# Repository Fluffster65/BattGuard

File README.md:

# BattGuard

BattGuard is a KiCad hardware design for a solar-assisted battery charger and power-management board. The project combines a 12 V charging path, protected power inputs, regulated system rails, battery monitoring, and an ESP32-S3 control interface on one board.

The design has progressed from an initial schematic into a nearly complete, routed PCB project. The current revision includes cleaned-up routing, test points, connector and switch footprints, populated protection and filtering components, and a shared component library with symbols, footprints, and 3D models.

## What the board includes

- **Battery charging:** BQ25756-based charger and power-path circuitry, with solar/charge input support and thermistor monitoring.
- **Power conversion:** 5 V buck regulation, 3.3 V regulation, and a boost circuit for the higher-voltage charging rail.
- **Protection:** reverse-polarity and reverse-current protection, transient suppression, input fusing, and protected power switching.
- **Measurement:** INA226 current/voltage monitoring with a dedicated shunt and I²C connectivity.
- **Control and telemetry:** ESP32-S3 header, GPIO breakouts, charge-enable control, status indicators, pushbuttons, and external connectors.
- **Serviceability:** labeled test points, modular connectors, and a board layout prepared for review and fabrication.

## Project status

The schematic and PCB are actively maintained and are at the late-stage design-review/fabrication-preparation phase. Recent work has focused on final trace routing, power-trace sizing, test-point and control-interface placement, silkscreen cleanup, and KiCad DRC cleanup. Fabrication, assembly, bring-up, and electrical validation are still separate steps and should not be inferred from the design files alone.

## Repository layout

```text
board/
├── BattGuard/       # Main schematic, PCB, rules, and project files
├── Datasheets/      # Component datasheets used during design
├── libs/
│   ├── 3dmodels/    # Local STEP models
│   ├── footprints/  # Shared TeamLib footprints
│   └── symbols/     # Shared KiCad symbols
├── fp-lib-table      # Project footprint-library configuration
└── sym-lib-table     # Project symbol-library configuration
```

The main KiCad project is `board/BattGuard/BattGuard.kicad_pro`. Library paths are project-relative, so the shared symbols, footprints, and models travel with the repository and do not require machine-specific absolute paths.

## Opening the project

1. Clone the repository.
2. Open `board/BattGuard/BattGuard.kicad_pro` in KiCad.
3. Confirm that the project loads the committed `TeamLib` symbol and footprint libraries.
4. Review the schematic, PCB, and design rules together before making layout changes.

## Contributing

When adding or changing a component, keep its symbol, footprint, and 3D model in the shared library structure under `board/libs/`. Verify that the part loads correctly in KiCad and that the schematic and PCB remain consistent. Avoid simultaneous edits to the same schematic sheet or PCB layout region, and tag known fabrication snapshots so board revisions remain traceable.

See [CONTRIBUTING.md](CONTRIBUTING.md) for the component-library workflow.

## Team

BattGuard is a Team 23 senior-design project by Brendan Duffy, Jon Mensah, Zachary Sydenstricker, and Tyler Wuthrich.

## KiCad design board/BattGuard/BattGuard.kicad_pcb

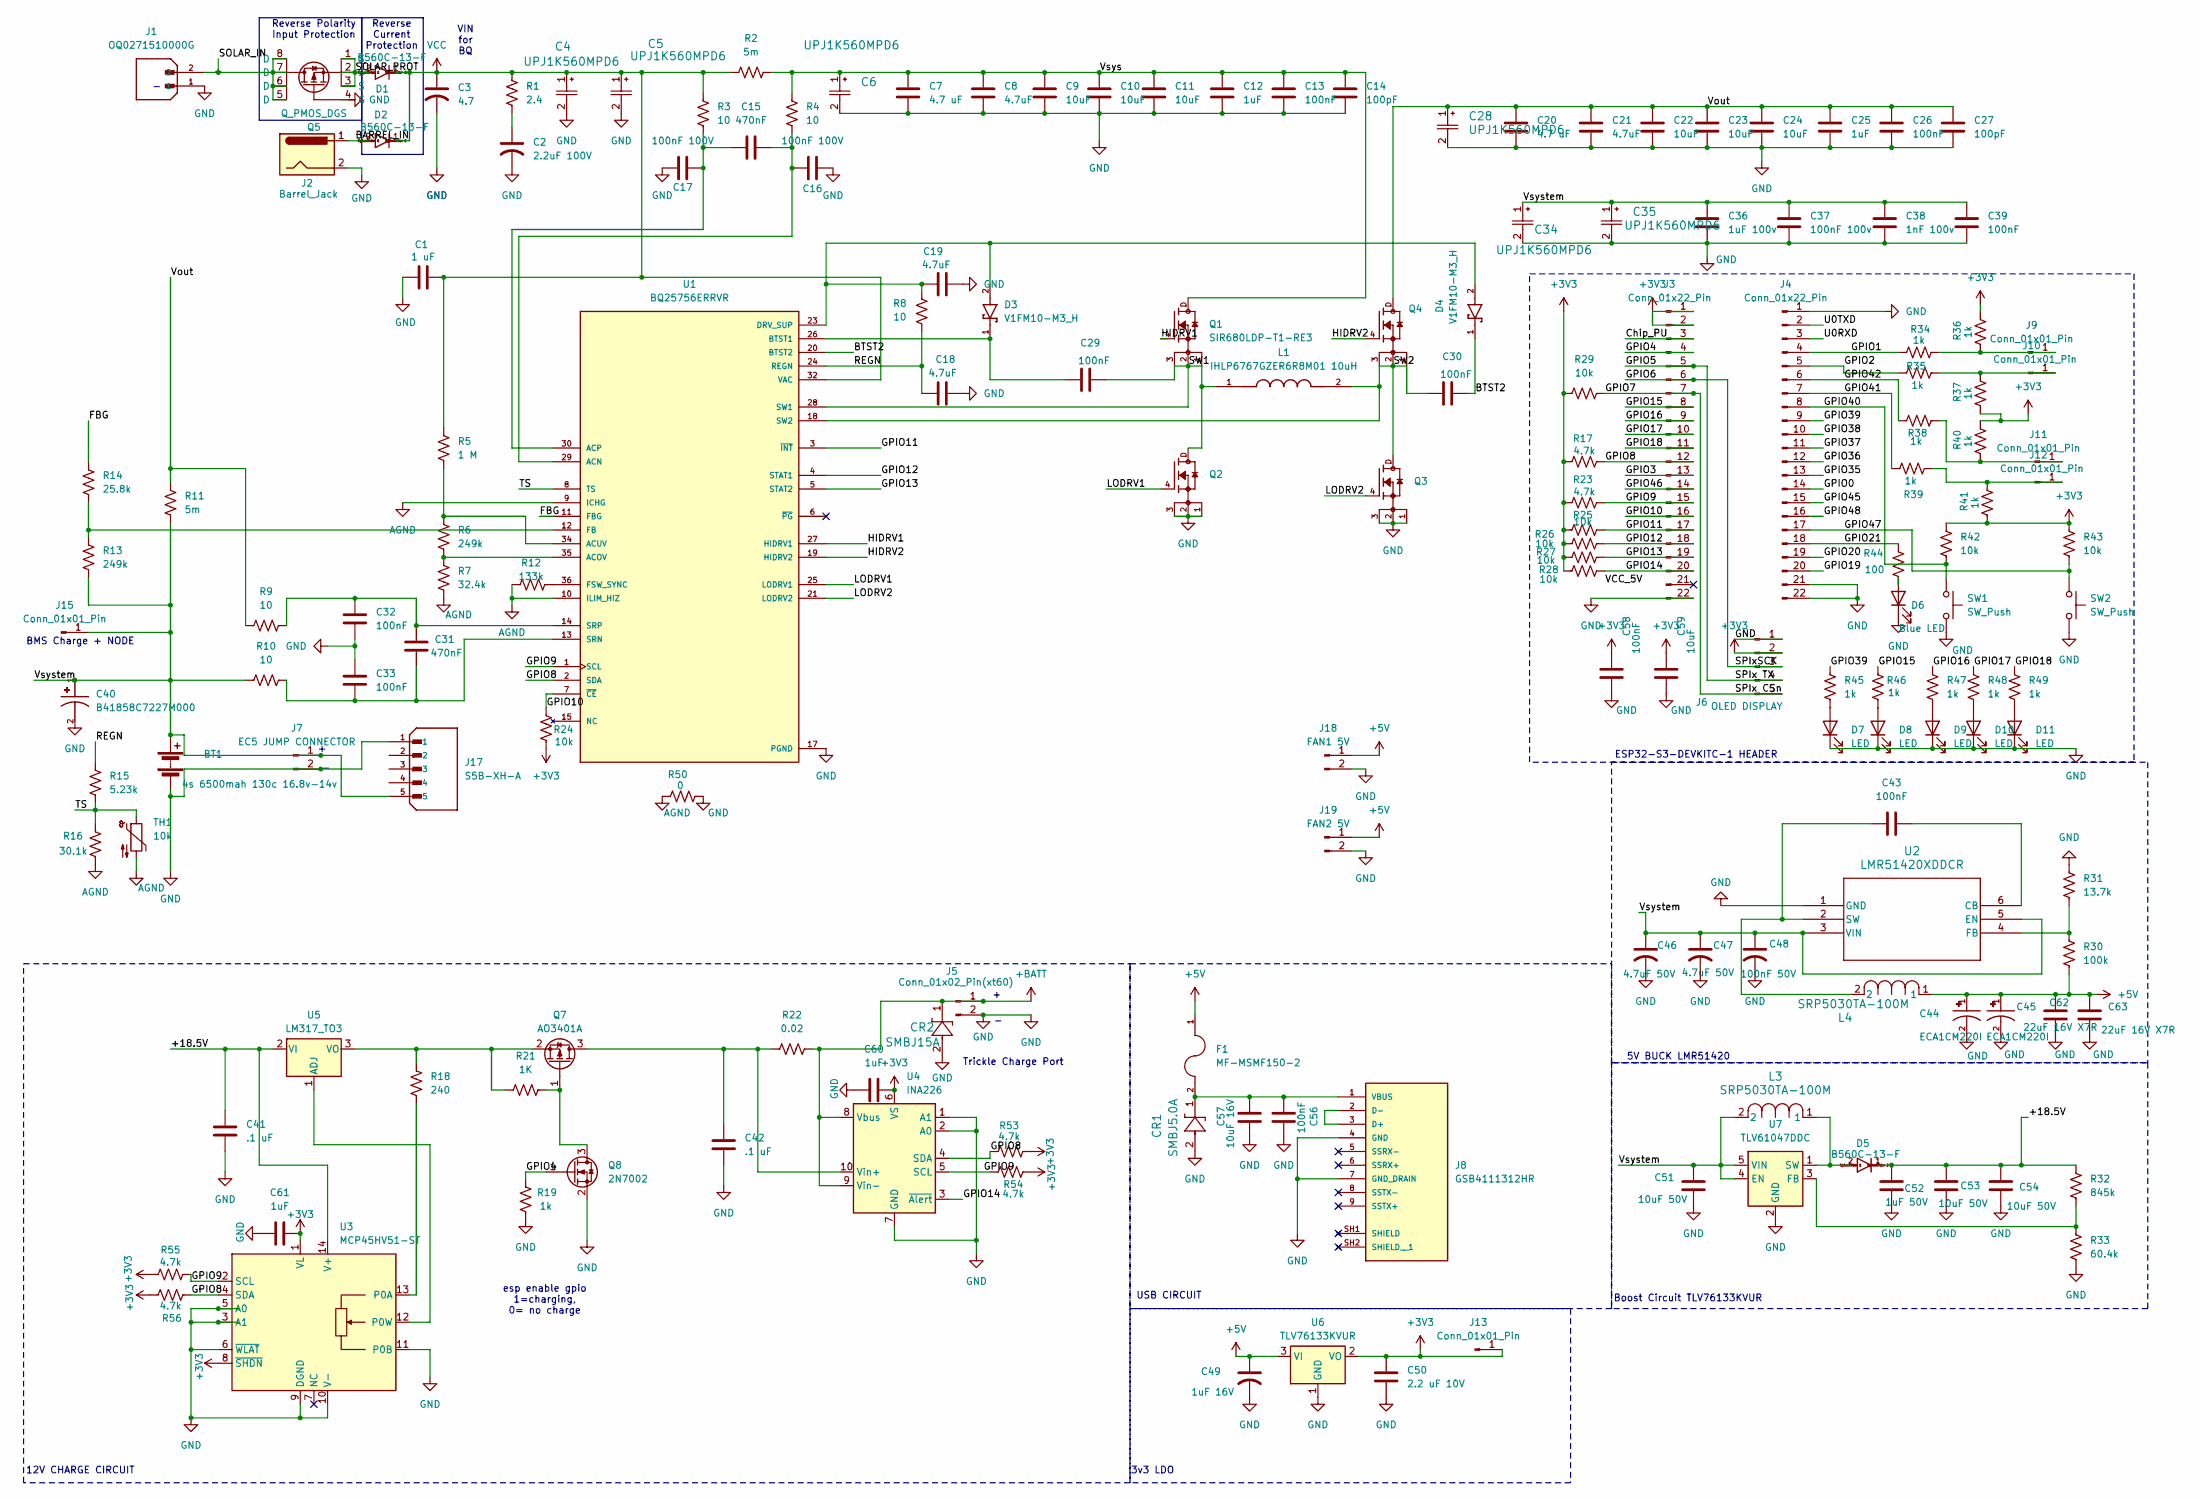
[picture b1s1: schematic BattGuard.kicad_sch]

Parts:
BT1: 4s 6500mah 130c 16.8v-14v
C1: 1 uF; C_0805_2012Metric
C2: 2.2uF 100V; C_1206_3216Metric
C3: 4.7; C_1210_3225Metric_Pad1.33x2.70mm_HandSolder
C4, C5, C6, C28, C34, C35: UPJ1K560MPD6; CAP_UPJ_10X15_NCH
C7, C20: 4.7 uF; C_0805_2012Metric
C8, C18, C19, C21: 4.7uF; C_0805_2012Metric
C9, C10, C11: 10uF; C_1210_3225Metric_Pad1.33x2.70mm_HandSolder
C12, C25, C60, C61: 1uF; C_0805_2012Metric
C13, C26, C29, C30, C32, C33, C39, C43, C56, C58: 100nF; C_0805_2012Metric
C14, C27: 100pF; C_0805_2012Metric
C15, C31: 470nF; C_0805_2012Metric
C16, C17: 100nF 100V; C_0805_2012Metric
C22, C23, C24, C59: 10uF; C_0805_2012Metric
C36: 1uF 100v; C_0805_2012Metric
C37: 100nF 100v; C_0805_2012Metric
C38: 1nF 100v; C_0805_2012Metric
C40: B41858C7227M000; CP_Radial_D10.0mm_P2.50mm; PARTREV 2018-10
C41, C42: .1 uF; C_0805_2012Metric
C44, C45: ECA1CM220I; CP_Radial_D10.0mm_P2.50mm; PARTREV 20-DEC-19
C46, C47: 4.7uF 50V; C_0805_2012Metric
C48: 100nF 50V; C_0805_2012Metric
C49: 1uF 16V; C_0805_2012Metric
C50: 2.2 uF 10V; C_0805_2012Metric
C51, C53, C54: 10uF 50V; C_1206_3216Metric_Pad1.33x1.80mm_HandSolder
C52: 1uF 50V; C_0805_2012Metric
C57: 10uF 16V; C_0805_2012Metric
C62, C63: 22uF 16V X7R; C_1206_3216Metric_Pad1.33x1.80mm_HandSolder
CR1: SMBJ5.0A; DO-214AASMB_J-BEND_LTF
CR2: SMBJ15A; DO-214AASMB_J-BEND_LTF
D1, D2, D5: B560C-13-F; D_SMC
D3, D4: V1FM10-M3_H; DIO_V1FM10-M3_H; PARTREV 13-May-2020; DigiKey_Part_Number 112-V1FM10-M3/HCT-ND
D6: Blue LED; LED_D1.8mm_W3.3mm_H2.4mm
D7, D8, D9, D10, D11: LED; LED_D1.8mm_W3.3mm_H2.4mm
F1: MF-MSMF150-2; FUSER_MF-MSMF150-2
J1: OQ0271510000G; PhoenixContact_GMSTBA_2,5_2-G_1x02_P7.50mm_Horizontal; PARTREV J
J2: Barrel_Jack; BarrelJack_CUI_PJ-063AH_Horizontal_CircularHoles
J3, J4: Conn_01x22_Pin; PinSocket_1x22_P2.54mm_Vertical
J5: Conn_01x02_Pin(xt60); AMASS_XT60PW-M_1x02_P7.20mm_Horizontal
J6: OLED DISPLAY; PinHeader_1x05_P2.54mm_Vertical
J7: EC5 JUMP CONNECTOR; AMASS_XT60PW-M_1x02_P7.20mm_Horizontal
J8: GSB4111312HR; USBA_receptacle; PARTREV B
J9, J10, J11, J12, J13: Conn_01x01_Pin; TestPoint_Pad_1.0x1.0mm
J15: Conn_01x01_Pin; MountingHole_2.2mm_M2_DIN965_Pad
J17: S5B-XH-A; JST_S5B-XH-A; PARTREV 27-1-20
J18: FAN1 5V; Wire_Pads_1x02_SMD_2.54
J19: FAN2 5V; Wire_Pads_1x02_SMD_2.54
L1: IHLP6767GZER6R8M01 10uH; L_Vishay_IHLP-6767; PARTREV 24-Nov-2023; DigiKey_Part_Number 541-1257-1-ND
L3, L4: SRP5030TA-100M; L_Bourns_SRP5030T
Q1, Q2, Q3, Q4: SIR680LDP-T1-RE3; TRANS_SIR680LDP-T1-RE3; PARTREV C
Q5: Q_PMOS_DGS; SOIC127P600X175-8N
Q7: AO3401A; SOT-23
Q8: 2N7002; SOT-23
R1: 2.4; R_0805_2012Metric
R2, R11: 5m; R_0805_2012Metric
R3, R4, R8, R9, R10: 10; R_0805_2012Metric
R5: 1 M; R_0805_2012Metric
R6, R13: 249k; R_0805_2012Metric
R7: 32.4k; R_0805_2012Metric
R12: 133k; R_0805_2012Metric
R14: 25.8k; R_0805_2012Metric
R15: 5.23k; R_0805_2012Metric
R16: 30.1k; R_0805_2012Metric
R17, R23, R53, R54, R55, R56: 4.7k; R_0805_2012Metric
R18: 240; R_0805_2012Metric
R19, R34, R35, R36, R37, R38, R39, R40, R41, R45, R46, R47, R48, R49: 1k; R_0805_2012Metric
R21: 1K; R_0805_2012Metric
R22: 0.02; R_0805_2012Metric
R24, R25, R26, R27, R28, R29, R42, R43: 10k; R_0805_2012Metric
R30: 100k; R_0805_2012Metric
R31: 13.7k; R_0805_2012Metric
R32: 845k; R_0805_2012Metric
R33: 60.4k; R_0805_2012Metric
R44: 100; R_0805_2012Metric
R50: 0; R_0805_2012Metric
SW1, SW2: SW_Push; Wire_Pads_1x02_SMD_2.54
TH1: 10k; R_0805_2012Metric
U1: BQ25756ERRVR; IC_BQ25756ERRVR; PARTREV November 2023; DigiKey_Part_Number 296-BQ25756ERRVRCT-ND
U2: LMR51420XDDCR; SOT23_DDC_TEX
U3: MCP45HV51-ST; TSSOP-14_4.4x5mm_P0.65mm
U4: INA226; TSSOP-10_3x3mm_P0.5mm
U5: LM317_TO3; TO-3
U6: TLV76133KVUR; SOT-223-3_TabPin2
U7: TLV61047DDC; SOT-23-5

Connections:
+5V: C44.1, C45.1, C49.1, C62.1, C63.1, F1.1, J18.1, J19.1, L4.1, R30.2, U6.3 (VI); also elsewhere on the board
+BATT: CR2.1, J5.1, R22.2, U4.8 (Vbus), U4.9 (Vin-)
/+18.5V: C41.1, C52.1, C53.1, C54.1, D5.1, R32.1, U3.14 (V+), U5.2 (VI); also elsewhere on the board
/BARREL_IN: D2.2, J2.1
/BTST2: C30.2, D4.1, U1.20 (BTST2)
/Chip_PU: J3.3
/FBG: R14.1, U1.11 (FBG)
/GPIO0: J4.14
/GPIO1: J4.4, R34.1
/GPIO2: J4.5, R35.1
/GPIO3: J3.13
/GPIO4: J3.4, Q8.1 (G), R19.2
/GPIO5: J3.5, J6.4
/GPIO6: J3.6, J6.3
/GPIO7: J3.7, J6.5, R29.2
/GPIO8: J3.12, R17.2, R53.2, R56.1, U1.2 (SDA), U3.4 (SDA), U4.4 (SDA)
/GPIO9: J3.15, R23.2, R54.2, R55.1, U1.1 (SCL), U3.2 (SCL), U4.5 (SCL)
/GPIO10: J3.16, R24.2, U1.7 (~CE)
/GPIO11: J3.17, R25.2, U1.3 (~INT)
/GPIO12: J3.18, R26.2, U1.4 (STAT1)
/GPIO13: J3.19, R27.2, U1.5 (STAT2)
/GPIO14: J3.20, R28.2, U4.3 (~Alert)
/GPIO15: J3.8, R46.1
/GPIO16: J3.9, R47.1
/GPIO17: J3.10, R48.1
/GPIO18: J3.11, R49.1
/GPIO19: J4.20
/GPIO20: J4.19
/GPIO21: J4.18, R44.1
/GPIO35: J4.13
/GPIO36: J4.12
/GPIO37: J4.11
/GPIO38: J4.10
/GPIO39: J4.9, R45.1
/GPIO40: J4.8, R42.2, SW1.1
/GPIO41: J4.7, R39.1
/GPIO42: J4.6, R38.1
/GPIO45: J4.15
/GPIO46: J3.14
/GPIO47: J4.17, R43.2, SW2.1
/GPIO48: J4.16
/HIDRV1: Q1.4, U1.27 (HIDRV1)
/HIDRV2: Q4.4, U1.19 (HIDRV2)
/LODRV1: Q2.4, U1.25 (LODRV1)
/LODRV2: Q3.4, U1.21 (LODRV2)
/REGN: C18.1, R8.1, R15.1, U1.24 (REGN)
/SOLAR_IN: J1.2, Q5.5 (D), Q5.6 (D), Q5.7 (D), Q5.8 (D)
/SOLAR_PROT: D1.2, Q5.1 (S), Q5.2 (S), Q5.3 (S)
/SW1: C29.2, L1.1, Q1.1, Q1.2, Q1.3, Q2.D, U1.28 (SW1)
/SW2: C30.1, L1.2, Q3.D, Q4.1, Q4.2, Q4.3, U1.18 (SW2)
/TS: R15.2, R16.1, TH1.1, U1.8 (TS); also elsewhere on the board
/U0RXD: J4.3
/U0TXD: J4.2
/Vout: C20.1, C21.1, C22.1, C23.1, C24.1, C25.1, C26.1, C27.1, C28.1, Q4.D, R9.1, R11.1
/Vsys: C6.1, C7.1, C8.1, C9.1, C10.1, C11.1, C12.1, C13.1, C14.1, Q1.D, R2.2, R4.1
/Vsystem: BT1.1 (+), C34.1, C35.1, C36.1, C37.1, C38.1, C39.1, C40.1, C46.1, C47.1, C48.1, C51.1, J7.1, J15.1 (Pin_1_1), J17.5, L3.2, R10.1, R11.2, R13.2, U2.3 (VIN), U2.5 (EN), U7.4 (EN), U7.5 (VIN)
AGND: R7.2, R12.1, R16.2, R50.1, TH1.2, U1.9 (ICHG), U1.10 (ILIM_HIZ); also elsewhere on the board
GND: BT1.2 (-), C1.1, C2.2, C3.2, C4.2, C5.2, C6.2, C7.2, C8.2, C9.2, C10.2, C11.2, C12.2, C13.2, C14.2, C16.2, C17.1, C18.2, C19.2, C20.2, C21.2, C22.2, C23.2, C24.2, C25.2, C26.2, C27.2, C28.2, C32.1, C33.2, C34.2, C35.2, C36.2, C37.2, C38.2, C39.2, C40.2, C41.2, C42.2, C44.2, C45.2, C46.2, C47.2, C48.2, C49.2, C50.2, C51.2, C52.2, C53.2, C54.2, C56.2, C57.2, C58.2, C59.2, C60.1, C61.1, C62.2, C63.2, CR1.2, CR2.2, D6.1 (K), D7.1 (K), D8.1 (K), D9.1 (K), D10.1 (K), D11.1 (K), J1.1, J2.2, J3.22, J4.1, J4.21, J4.22, J5.2, J6.1, J7.2, J8.4 (GND), J8.7 (GND_DRAIN), J17.1, J18.2, J19.2, Q2.1, Q2.2, Q2.3, Q3.1, Q3.2, Q3.3, Q5.4 (G), Q8.2 (S), R19.1, R31.1, R33.2, R50.2, SW1.2, SW2.2, U1.17 (PGND), U1.22 (PGND), U1.37 (PGND), U2.1 (GND), U3.3 (A1), U3.5 (A0), U3.6 (~WLAT), U3.9 (DGND), U3.10 (V-), U3.11 (P0B), U4.1 (A1), U4.2 (A0), U4.7 (GND), U6.1 (GND), U7.2 (GND); also elsewhere on the board
unnamed: C2.1, R1.2
unnamed: D6.2 (A), R44.2
unnamed: D7.2 (A), R45.2
unnamed: D8.2 (A), R46.2
unnamed: D9.2 (A), R47.2
unnamed: D10.2 (A), R48.2
unnamed: D11.2 (A), R49.2
unnamed: J8.2 (D-), J8.3 (D+)
unnamed: C56.1, C57.1, CR1.1, F1.2, J8.1 (VBUS)
unnamed: J10.1 (Pin_1_1), R35.2, R37.2
unnamed: J11.1 (Pin_1_1), R38.2, R40.1
unnamed: J12.1 (Pin_1_1), R39.2, R41.2
unnamed: C42.1, Q7.3 (D), R22.1, U4.10 (Vin+)
unnamed: Q7.1 (G), Q8.3 (D), R21.2
unnamed: Q7.2 (S), R18.1, R21.1, U5.3 (VO)
unnamed: C15.2, C16.1, R4.2, U1.29 (ACN)
unnamed: R6.2, R7.1, U1.35 (ACOV)
unnamed: C15.1, C17.2, R3.2, U1.30 (ACP)
unnamed: R5.2, R6.1, U1.34 (ACUV)
unnamed: C29.1, D3.1, U1.26 (BTST1)
unnamed: C19.1, D3.2, D4.2, R8.2, U1.23 (DRV_SUP)
unnamed: R13.1, R14.2, U1.12 (FB)
unnamed: R12.2, U1.36 (FSW_SYNC)
unnamed: C31.1, C33.1, R10.2, U1.13 (SRN)
unnamed: C31.2, C32.2, R9.2, U1.14 (SRP)
unnamed: C43.2, U2.6 (CB)
unnamed: R30.1, R31.2, U2.4 (FB)
unnamed: C43.1, L4.2, U2.2 (SW)
unnamed: R18.2, U3.13 (P0A)
unnamed: U3.12 (P0W), U5.1 (ADJ)
unnamed: R32.2, R33.1, U7.3 (FB)
unnamed: D5.2, L3.1, U7.1 (SW)
VCC: C1.2, C3.1, C4.1, C5.1, D1.1, D2.1, R1.1, R2.1, R3.1, R5.1, U1.32 (VAC), U1.33 (VAC)

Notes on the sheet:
Reverse Current Protection
Boost Circuit TLV76133KVUR
Trickle Charge Port
3v3 LDO
GND
12V CHARGE CIRCUIT
BMS Charge + NODE
ESP32-S3-DEVKITC-1 HEADER
5V BUCK LMR51420
USB CIRCUIT
VIN for BQ
esp enable gpio 1=charging, 0= no charge
Reverse Polarity Input Protection

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
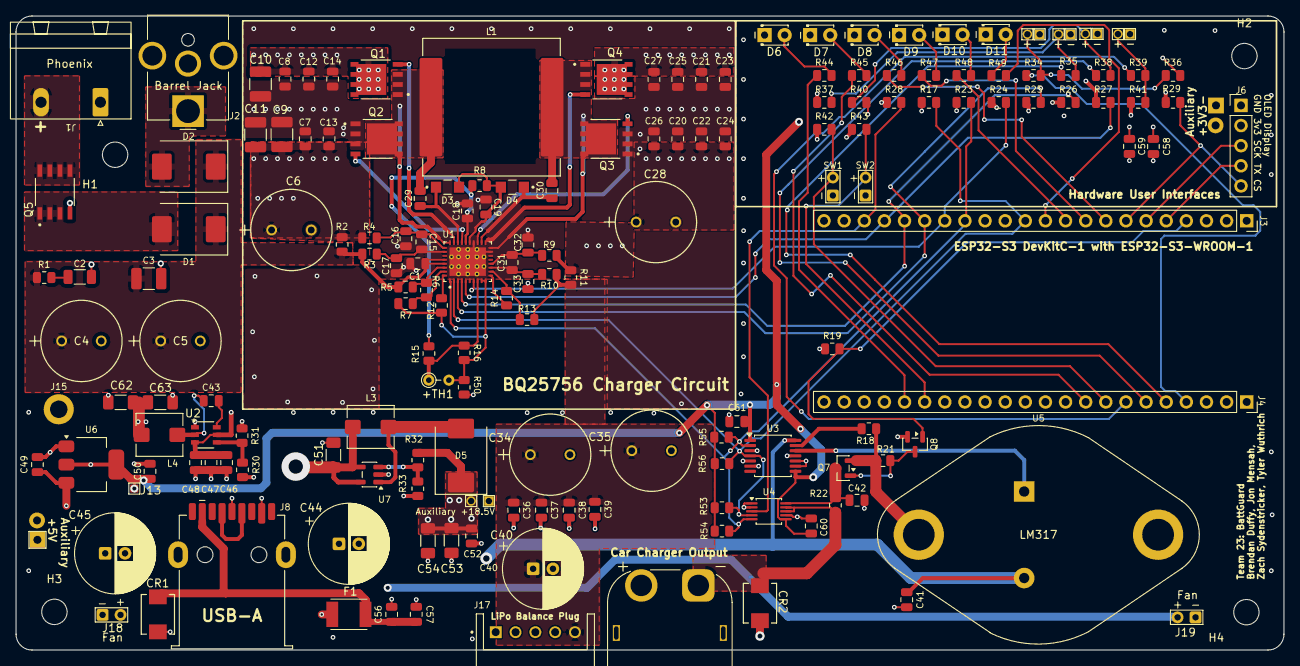
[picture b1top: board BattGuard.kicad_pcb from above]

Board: 4 copper layers, 160.0 x 80.0 mm, 179 parts (0 on the bottom side), 79 nets.

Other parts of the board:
+TH1: 10k; R_Axial_DIN0204_L3.6mm_D1.6mm_P2.54mm_Vertical
GND: Conn_01x01_Pin; GND_Pin_1.0x1.0mm
GND#2, GND#3, GND#4, GND#5, GND#6, GND#7: Conn_01x01_Pin; GND_Pin_1.0x1.0mm
H1, H2, H3, H4: MountingHole_3.2mm_M3
J9#2, J9#3, J9#4: Conn_01x01_Pin; TestPoint_Pad_1.0x1.0mm

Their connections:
+5V: J9#4.1 (Pin_1_1); also elsewhere on the board
/+18.5V: J9#2.1 (Pin_1_1); also elsewhere on the board
/TS: +TH1.1; also elsewhere on the board
AGND: +TH1.2; also elsewhere on the board
GND: GND.1 (Pin_1_1), GND#2.1 (Pin_1_1), GND#3.1 (Pin_1_1), GND#4.1 (Pin_1_1), GND#5.1 (Pin_1_1), GND#6.1 (Pin_1_1), GND#7.1 (Pin_1_1); also elsewhere on the board
